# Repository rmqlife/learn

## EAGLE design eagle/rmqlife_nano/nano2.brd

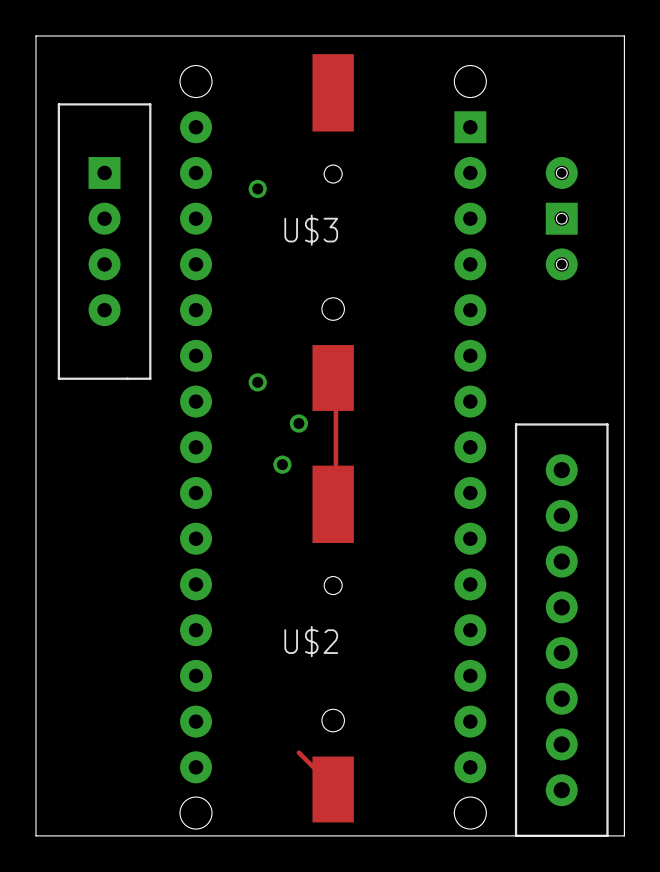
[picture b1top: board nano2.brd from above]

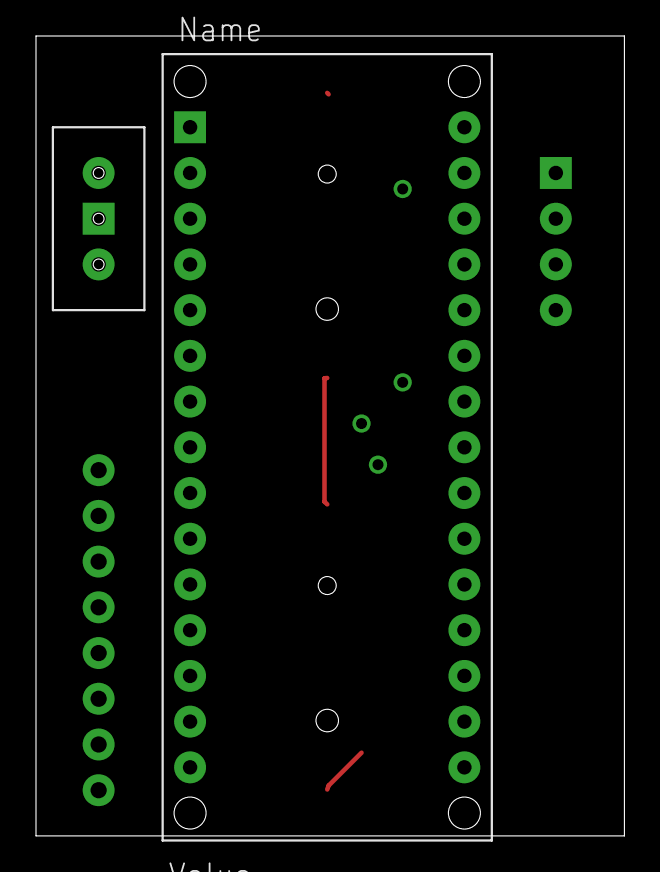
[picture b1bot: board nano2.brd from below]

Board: 2 copper layers, 32.7 x 44.4 mm, 6 parts (2 on the bottom side), 11 nets.

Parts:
U$1: ARDUINONANO; PDIP-32
U$2, U$3: CR1220-HOLDER; HARWIN-CR1220
U$4: GY85
U$5: HC06
U$7: KEY_SMALL

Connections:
unnamed: U$1.+5V, U$4.VCC_IN, U$5.VCC, U$7.VCC
unnamed: U$1.VIN, U$2.POS
unnamed: U$1.GND1, U$3.NEG, U$4.GND
unnamed: U$1.3V3, U$4.3.3V
unnamed: U$1.GND, U$5.GND, U$7.GND
unnamed: U$1.D8, U$7.DAT
unnamed: U$2.NEG, U$3.POS
unnamed: U$1.D1/TX, U$5.TXD
unnamed: U$1.D0/RX, U$5.RXD
unnamed: U$1.A5, U$4.SCL
unnamed: U$1.A4, U$4.SDA

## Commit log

2016-08-13 init
2016-08-13 fix opencv
